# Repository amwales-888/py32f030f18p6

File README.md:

# py32f030f18p6
Simple breakout board for py32f030f18p6

- 3.3v LDO powered from 5V USB.
- UART connectivity to USB via ch340k optionally connected using jumpers.
- ARM SWD programming interface header.
- All other pins are broken out to headers.
- 1 LED optionally connected to pin PB5 using jumper.
- 1 Button optionally connected to pin PA8 using jumper.
- 1 Button connected to RESET pin, pulled high.
- Booloader selected by putting jumper across BOOT0 and 3v3 pins

<table>
  <tr>
    <td> </td>
    <td> </td>
  </tr>
  <tr>
    <td> </td>
    <td> </td>
  </tr>
  <tr>
    <td> </td>
    <td> </td>
  </tr>
  <tr>
    <td> </td>
  </tr>
</table>

Resources

<li>https://www.puyasemi.com/en/py32_series.html</li>
<li>https://www.eevblog.com/forum/microcontrollers/$0-11-py32f002a-m0-24mhz-320kb-actually-324kb-more-peripherals/</li>
<li>https://www.cnblogs.com/milton/p/18168592</li>
<li>https://github.com/IOsetting/py32f0-template/tree/main</li>
<li>https://www.cnblogs.com/milton/p/17111286.html</li>
<li>https://www.cnblogs.com/milton/p/18168592</li>
<li>https://www.lcsc.com/product-detail/C3018715.html</li>

<BR>

Notes - Assembled board with 24Mhz crystal, flashed and tested with simple LED blink/UART code via the connected via USB. Used jlink clone connected via SWD and built with keil uvision, connected jlink to reset pin. Verified running at 48Mhz by timing blink rate of LED. Have not tested bootloader configuration yet.

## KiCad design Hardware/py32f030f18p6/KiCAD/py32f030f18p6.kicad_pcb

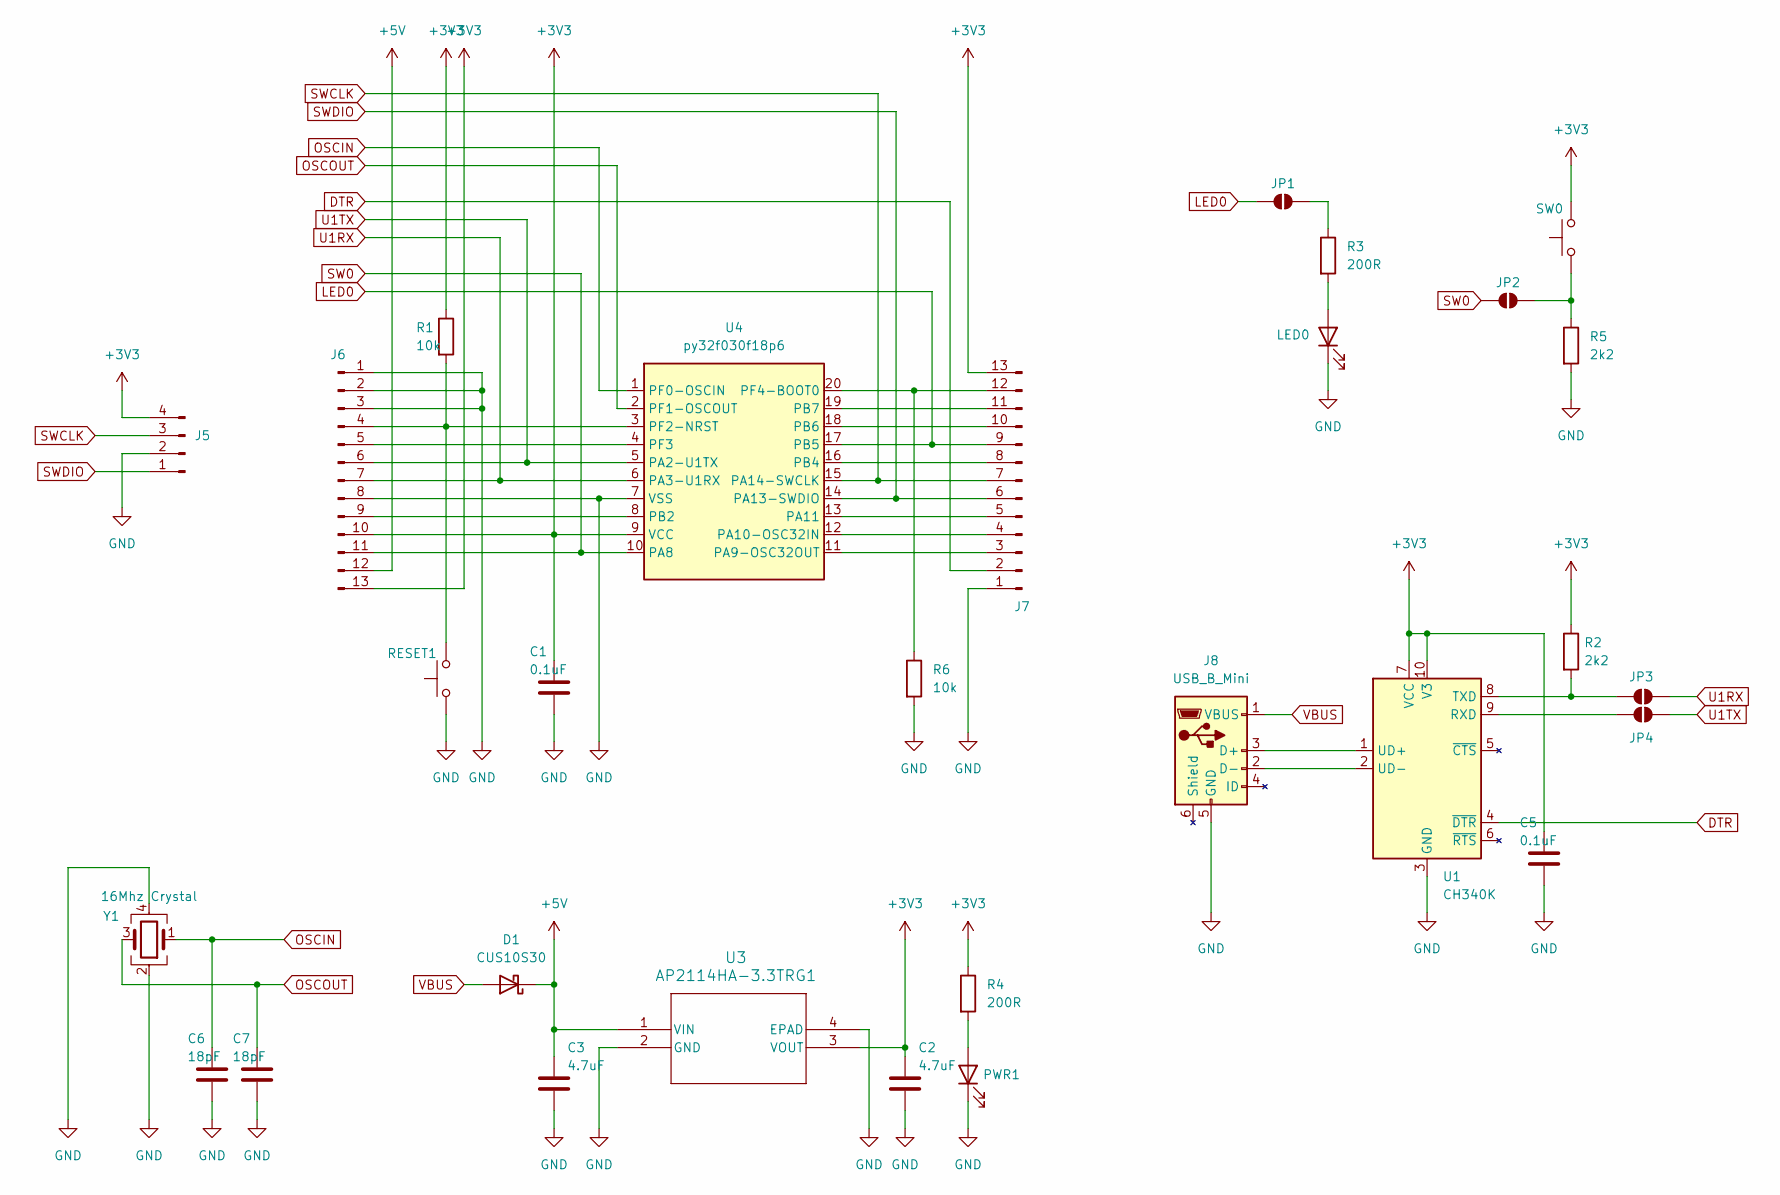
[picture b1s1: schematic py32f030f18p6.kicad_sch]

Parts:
C1, C5: 0.1uF; C_0805_2012Metric_Pad1.18x1.45mm_HandSolder
C2, C3: 4.7uF; C_1206_3216Metric_Pad1.33x1.80mm_HandSolder
C6, C7: 18pF; C_0603_1608Metric
D1: CUS10S30; D_SOD-323-H; LCSC Part# C146335
J5: Conn_01x04_Pin; PinHeader_1x04_P2.54mm_Vertical
J6, J7: Conn_01x13_Pin; PinHeader_1x13_P2.54mm_Vertical
J8: USB_B_Mini; USB_Mini-B_Lumberg_2486_01_Horizontal; LCSC Part# C105424
JP1, JP2, JP3, JP4: SolderJumper_2_Open; SolderJumper-2_P1.3mm_Open_RoundedPad1.0x1.5mm
LED0: LED; LED_0603_1608Metric_Pad1.05x0.95mm_HandSolder
PWR1: LED; LED_0603_1608Metric_Pad1.05x0.95mm_HandSolder
R1, R6: 10k; R_0805_2012Metric_Pad1.20x1.40mm_HandSolder
R2, R5: 2k2; R_0805_2012Metric_Pad1.20x1.40mm_HandSolder
R3, R4: 200R; R_0805_2012Metric_Pad1.20x1.40mm_HandSolder
RESET1: SW_Push; SW_Tactile_SPST_NO_Straight_CK_PTS636Sx25SMTRLFS
SW0: SW_Push; SW_Tactile_SPST_NO_Straight_CK_PTS636Sx25SMTRLFS
U1: CH340K; SSOP-10-1EP_3.9x4.9mm_P1mm_EP2.1x3.3mm; LCSC Part# C968586
U3: AP2114HA-3.3TRG1; SOT-223_DIO; LCSC Part# C460314
U4: py32f030f18p6; TSSOP-20_4.4x6.5mm_P0.65mm; LCSC Part# C3018715
Y1: 16Mhz Crystal; CDFN-4_2.5x3.2mm_P2.1mm; LCSC Part# C41383242

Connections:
+3V3: C1.1, C2.1, C5.1, J5.4, J6.10, J6.13, J7.13, R1.1, R2.1, R4.1, SW0.2, U1.7 (VCC), U1.10 (V3), U3.3 (VOUT), U4.9 (VCC)
+5V: C3.1, D1.1 (K), J6.12, U3.1 (VIN)
DTR: J7.2, U1.4 (~DTR)
GND: C1.2, C2.2, C3.2, C5.2, C6.2, C7.2, J5.2, J6.1, J6.2, J6.3, J6.8, J7.1, J8.5 (GND), LED0.1 (K), PWR1.1 (K), R5.2, R6.2, RESET1.1, U1.3 (GND), U3.2 (GND), U3.4 (EPAD), U4.7 (VSS), Y1.2, Y1.4
LED0: J7.9, JP1.1 (A), U4.17 (PB5)
unnamed: J6.4, R1.2, RESET1.2, U4.3 (PF2-NRST)
unnamed: J6.5, U4.4 (PF3)
unnamed: J6.9, U4.8 (PB2)
unnamed: J7.3, U4.11 (PA9-OSC32OUT)
unnamed: J7.4, U4.12 (PA10-OSC32IN)
unnamed: J7.5, U4.13 (PA11)
unnamed: J7.8, U4.16 (PB4)
unnamed: J7.10, U4.18 (PB6)
unnamed: J7.11, U4.19 (PB7)
unnamed: J7.12, R6.1, U4.20 (PF4-BOOT0)
unnamed: J8.3 (D+), U1.1 (UD+)
unnamed: J8.2 (D-), U1.2 (UD-)
unnamed: JP1.2 (B), R3.1
unnamed: JP2.2 (B), R5.1, SW0.1
unnamed: JP3.1 (A), R2.2, U1.8 (TXD)
unnamed: JP4.1 (A), U1.9 (RXD)
unnamed: LED0.2 (A), R3.2
unnamed: PWR1.2 (A), R4.2
OSCIN: C6.1, U4.1 (PF0-OSCIN), Y1.1
OSCOUT: C7.1, U4.2 (PF1-OSCOUT), Y1.3
SW0: J6.11, JP2.1 (A), U4.10 (PA8)
SWCLK: J5.3, J7.7, U4.15 (PA14-SWCLK)
SWDIO: J5.1, J7.6, U4.14 (PA13-SWDIO)
U1RX: J6.7, JP3.2 (B), U4.6 (PA3-U1RX)
U1TX: J6.6, JP4.2 (B), U4.5 (PA2-U1TX)
VBUS: D1.2 (A), J8.1 (VBUS)

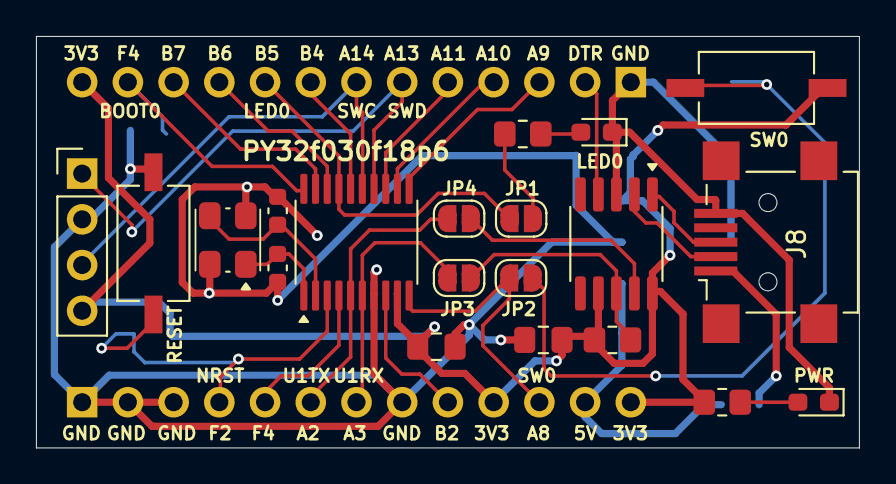
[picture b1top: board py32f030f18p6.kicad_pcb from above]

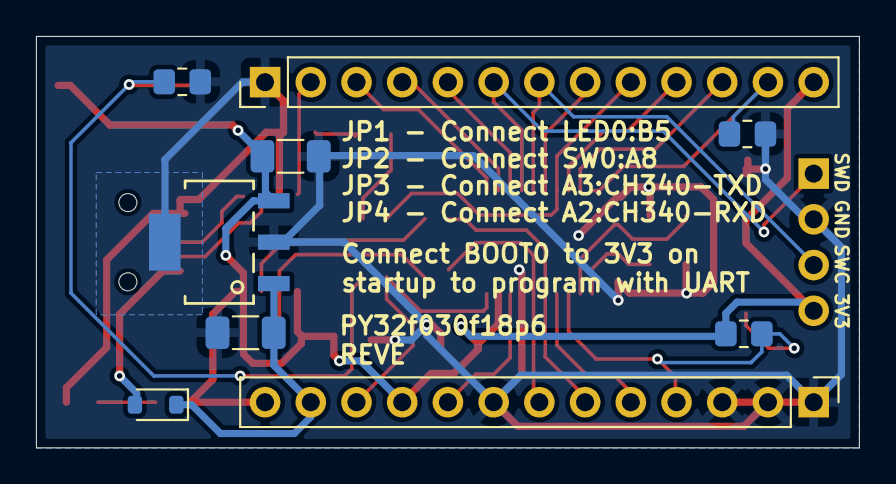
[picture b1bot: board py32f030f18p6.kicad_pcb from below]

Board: 2 copper layers, 45.7 x 22.9 mm, 29 parts (9 on the bottom side), 31 nets.

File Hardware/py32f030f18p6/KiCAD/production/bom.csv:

Designator,Footprint,Quantity,Value,LCSC Part #
"C1, C5",0805,2,0.1uF,
"C2, C3",1206,2,4.7uF,
"C6, C7",0603,2,18pF,
D1,D_SOD-323,1,TB6612FNG,
J5,PinHeader_1x04_P2.54mm_Vertical,1,Conn_01x04_Pin,
"J6, J7",PinHeader_1x13_P2.54mm_Vertical,2,Conn_01x13_Pin,
J8,USB_Mini-B_Lumberg_2486_01_Horizontal,1,USB_B_Mini,
"LED0, PWR1",0603,2,LED,
"R1, R6",0805,2,10k,
"R2, R5",0805,2,2k2,
"R3, R4",0805,2,200R,
"RESET1, SW0",SW_Tactile_SPST_NO_Straight_CK_PTS636Sx25SMTRLFS,2,SW_Push,
U1,SSOP-10-1EP_3.9x4.9mm_P1mm_EP2.1x3.3mm,1,CH340K,
U3,SOT-223_DIO,1,AP2114HA-3.3TRG1,
U4,TSSOP-20_4.4x6.5mm_P0.65mm,1,py32f030f18p6,
Y1,CDFN-4_2.5x3.2mm_P2.1mm,1,16Mhz Crystal,

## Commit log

2024-09-23 Initial checkin
2024-09-26 Remove button replace with header, removed reset pin
    Replaced the boot button with a header, removed reset pin
2024-09-27 Generate latest gerbers
2024-09-29 Added led blink firmware
    Added eaxmple led blink firmware, the resulting .hex file can be flashed to the board by plugging in the USB enabling the bootloader pins, running the PY32_IspTool connecting and downloading.
2024-10-24 blink portb pin5 thats connected to a led
2025-01-28 Added missing pullup on RX to fix bootloader issue, updated the firmware so it outputs message on uart
2025-01-28 Issue with silk screen, GND pin was labelled 3v3
2025-01-29 Added windows py32_IspTool and other documentation
2026-04-17 Reformat Directory Structure and Add KiCAD version
    Reformat Directory Structure and Add KiCAD version
2026-04-24 Deprecated old eagle layout
    Deprecated old eagle layout
2026-04-25 Update README with new resource links
    Added additional resources for the py32 series.
2026-04-25 Update README with firmware notes
    Add notes regarding firmware and board changes.
2026-04-25 Add new link to README for product detail
2026-05-21 Updated firmware, changed pad size on diode to make more hand solder friendly
    Build board and verified blink led on latest board back from jlpcb, programmed with swd using reset pin, changed pad size for diode as it was tiny.
2026-05-22 Added photos
2026-05-22 Revise notes on board assembly and testing process
    Updated notes section to reflect changes in board assembly and testing.
2026-05-22 Added 24MHz External Crystal and to run at 48MHz
2026-05-22 Revise assembly notes for board configuration
    Updated notes to reflect the addition of a 24MHz crystal and verification of 48MHz operation.
